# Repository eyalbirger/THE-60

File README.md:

The 60 is a split wireless/wired (pro micro and n!n) keyboard with mx switches, a screen option and harry potter art :)
its a lily58 like keyboard, but with an extra key and a stager that fits my hand better. maybe this will have a v3 with a knob (and more!), 
but i dont know if i want to spend money on that if this is a perfectly good keeb. anyway if there is a problem feel free to massege me.
i will not have a guide because realisticly im the only one thats ever gonna see this repo, so there is no point in having one. all the file
(and a complete bom) are also in here (https://www.nexprint.com/en/models/G7307162) so search it there. again im not gonna make a bom here cause 
no one is going to see this.

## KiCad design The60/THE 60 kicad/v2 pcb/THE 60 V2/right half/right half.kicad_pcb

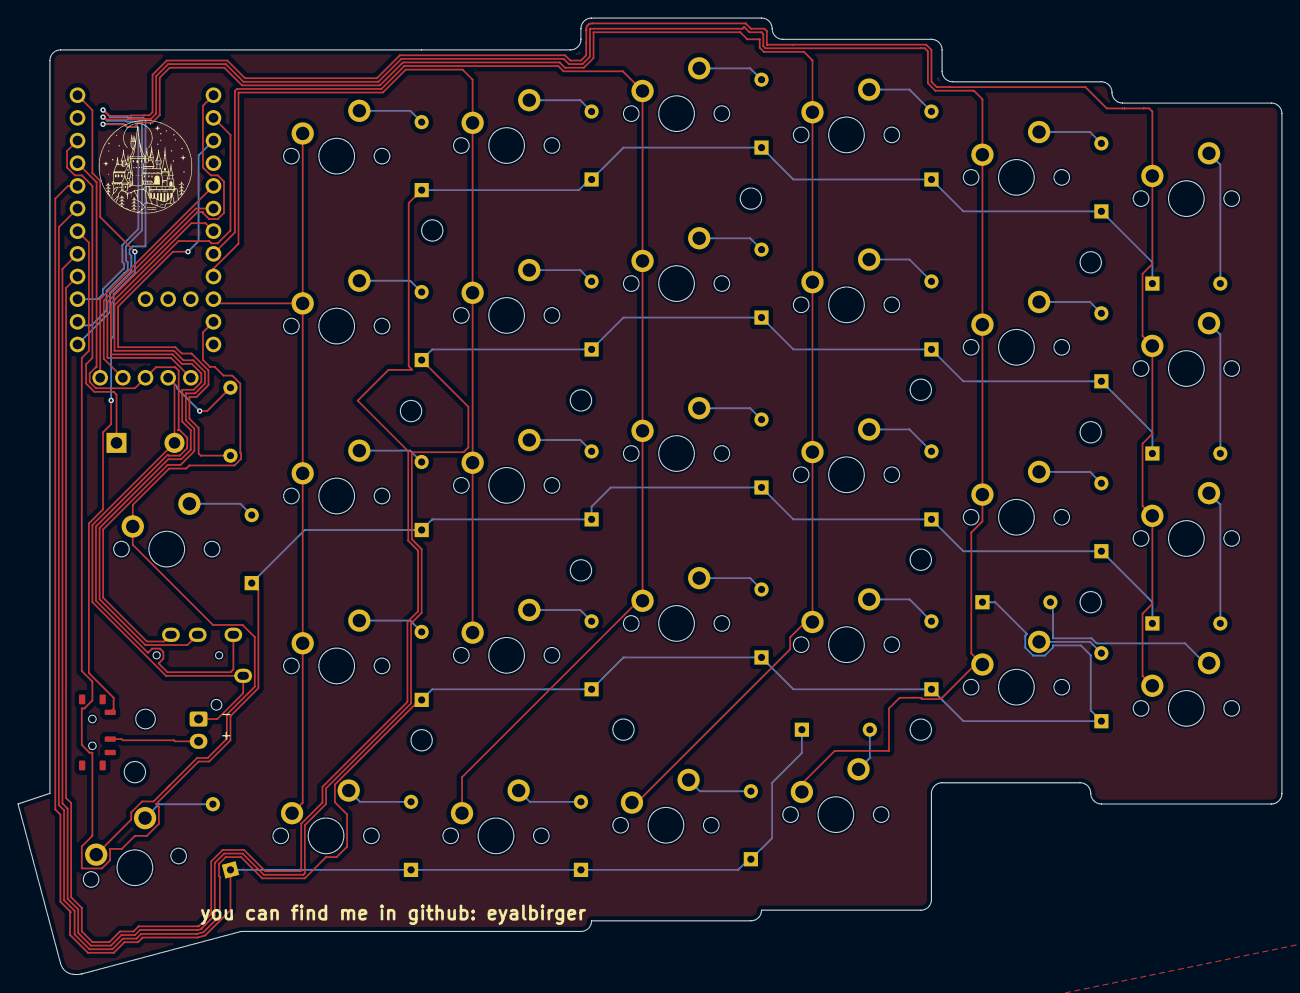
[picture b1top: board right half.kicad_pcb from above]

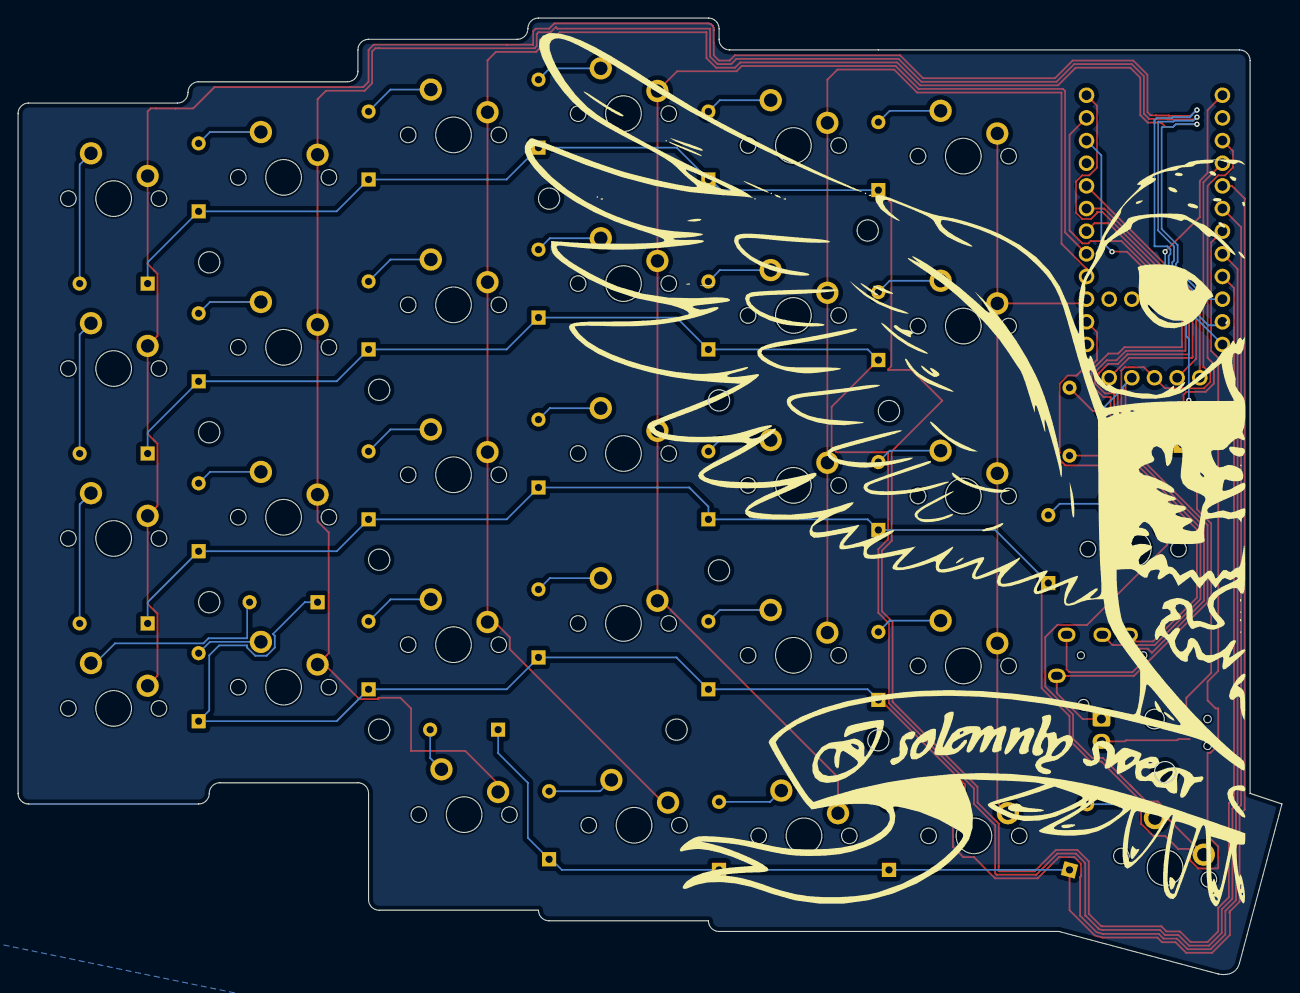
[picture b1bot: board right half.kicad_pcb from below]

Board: 2 copper layers, 141.7 x 107.2 mm, 68 parts (31 on the bottom side), 53 nets.

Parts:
D1, D2, D3, D4, D5, D6, D7, D8, D9, D10, D11, D12, D13, D14, D15, D16, D17, D18, D19, D20, D21, D22, D23, D24, D25, D26, D27, D28, D29, D59: Diode; Diode_DO-35
Display1: nice!view; nice_view
H6: MountingHole; MountingHole_2.2mm_M2
J1: Conn_01x02_Socket; JST_XH_B2B-XH-AM_1x02_P2.50mm_Vertical
R1: Resistor; R_Axial_DIN0207_L6.3mm_D2.5mm_P7.62mm_Horizontal
S1, S2, S3, S4, S5, S6, S7, S8, S9, S10, S11, S12, S13, S14, S15, S16, S17, S18, S19, S20, S21, S22, S23, S24, S25, S26, S27, S28, S29, S59: Keyswitch; MX_PCB_1.00u
SW1: Switch; Switch_MSK12C02
SW2: Switch; Button_MJTP1243
U2: Nice_Nano_V2; Nice_Nano_V2_Flipped
U3: TRRS; TRRS_PJ-320A

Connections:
19: U2.2 (0), U3.4 (RING2)
20: U2.7 (4), U3.3 (RING1)
+: J1.2, SW1.2
-: R1.1, U2.3 (GND)
unnamed: D1.2 (A), S1.2
unnamed: D2.2 (A), S2.2
unnamed: D3.2 (A), S3.2
unnamed: D4.2 (A), S4.2
unnamed: D5.2 (A), S5.2
unnamed: D6.2 (A), S6.2
unnamed: D7.2 (A), S7.2
unnamed: D8.2 (A), S8.2
unnamed: D9.2 (A), S9.2
unnamed: D10.2 (A), S10.2
unnamed: D11.2 (A), S11.2
unnamed: D12.2 (A), S12.2
unnamed: D13.2 (A), S13.2
unnamed: D14.2 (A), S14.2
unnamed: D15.2 (A), S15.2
unnamed: D16.2 (A), S16.2
unnamed: D17.2 (A), S17.2
unnamed: D18.2 (A), S18.2
unnamed: D19.2 (A), S19.2
unnamed: D20.2 (A), S20.2
unnamed: D21.2 (A), S21.2
unnamed: D22.2 (A), S22.2
unnamed: D23.2 (A), S23.2
unnamed: D24.2 (A), S24.2
unnamed: D25.2 (A), S25.2
unnamed: D26.2 (A), S26.2
unnamed: D27.2 (A), S27.2
unnamed: D28.2 (A), S28.2
unnamed: D29.2 (A), S29.2
unnamed: D59.2 (A), S59.2
b+: SW1.1, U2.24 (B+)
column 0: S1.1, S7.1, S13.1, S19.1, S59.1, U2.10 (7)
column 1: S2.1, S8.1, S14.1, S20.1, U2.9 (6)
column 2: S3.1, S9.1, S15.1, S21.1, S28.1, U2.8 (5)
column 3: S4.1, S10.1, S16.1, S22.1, S27.1, U2.15 (14)
column 4: S5.1, S11.1, S17.1, S23.1, S26.1, U2.14 (16)
column 5: S6.1, S12.1, S18.1, S24.1, U2.13 (10)
column -1: S25.1, S29.1, U2.11 (8)
cs: Display1.5 (CS), U2.1
gnd: Display1.4 (GND), J1.1, R1.2, SW2.2, U3.1 (SLEEVE)
mosi: Display1.1 (MOSI), U2.5 (2)
row 0: D1.1 (K), D2.1 (K), D3.1 (K), D4.1 (K), D5.1 (K), D6.1 (K), U2.16 (15)
row 1: D7.1 (K), D8.1 (K), D9.1 (K), D10.1 (K), D11.1 (K), D12.1 (K), U2.17 (18)
row 2: D13.1 (K), D14.1 (K), D15.1 (K), D16.1 (K), D17.1 (K), D18.1 (K), D25.1 (K), U2.18 (19)
row 3: D19.1 (K), D20.1 (K), D21.1 (K), D22.1 (K), D23.1 (K), D24.1 (K), U2.19 (20)
row 4: D26.1 (K), D27.1 (K), D28.1 (K), D29.1 (K), D59.1 (K), U2.20 (21)
rst: SW2.1, U2.22 (RST)
sck: Display1.2 (SCK), U2.6 (3)
vcc: Display1.3 (VCC), U2.21 (3.3v), U3.2 (TIP)

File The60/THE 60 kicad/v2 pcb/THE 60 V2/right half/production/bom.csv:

Designator,Footprint,Quantity,Value,LCSC Part #
"D1, D10, D11, D12, D13, D14, D15, D16, D17, D18, D19, D2, D20, D21, D22, D23, D24, D25, D26, D27, D28, D29, D3, D4, D5, D59, D6, D7, D8, D9",Diode_DO-35,30,Diode,
DISPLAY1,nice_view,1,nice!view,
J1,JST_XH_B2B-XH-AM_1x02_P2.50mm_Vertical,1,Conn_01x02_Socket,
R1,R_Axial_DIN0207_L6.3mm_D2.5mm_P7.62mm_Horizontal,1,Resistor,
"S1, S10, S11, S12, S13, S14, S15, S16, S17, S18, S19, S2, S20, S21, S22, S23, S24, S25, S26, S27, S28, S29, S3, S4, S5, S59, S6, S7, S8, S9",MX_PCB_1.00u,30,Keyswitch,
SW1,Switch_MSK12C02,1,Switch,
SW2,Button_MJTP1243,1,Switch,
U2,Nice_Nano_V2_Flipped,1,Nice_Nano_V2,
U3,TRRS_PJ-320A,1,TRRS,

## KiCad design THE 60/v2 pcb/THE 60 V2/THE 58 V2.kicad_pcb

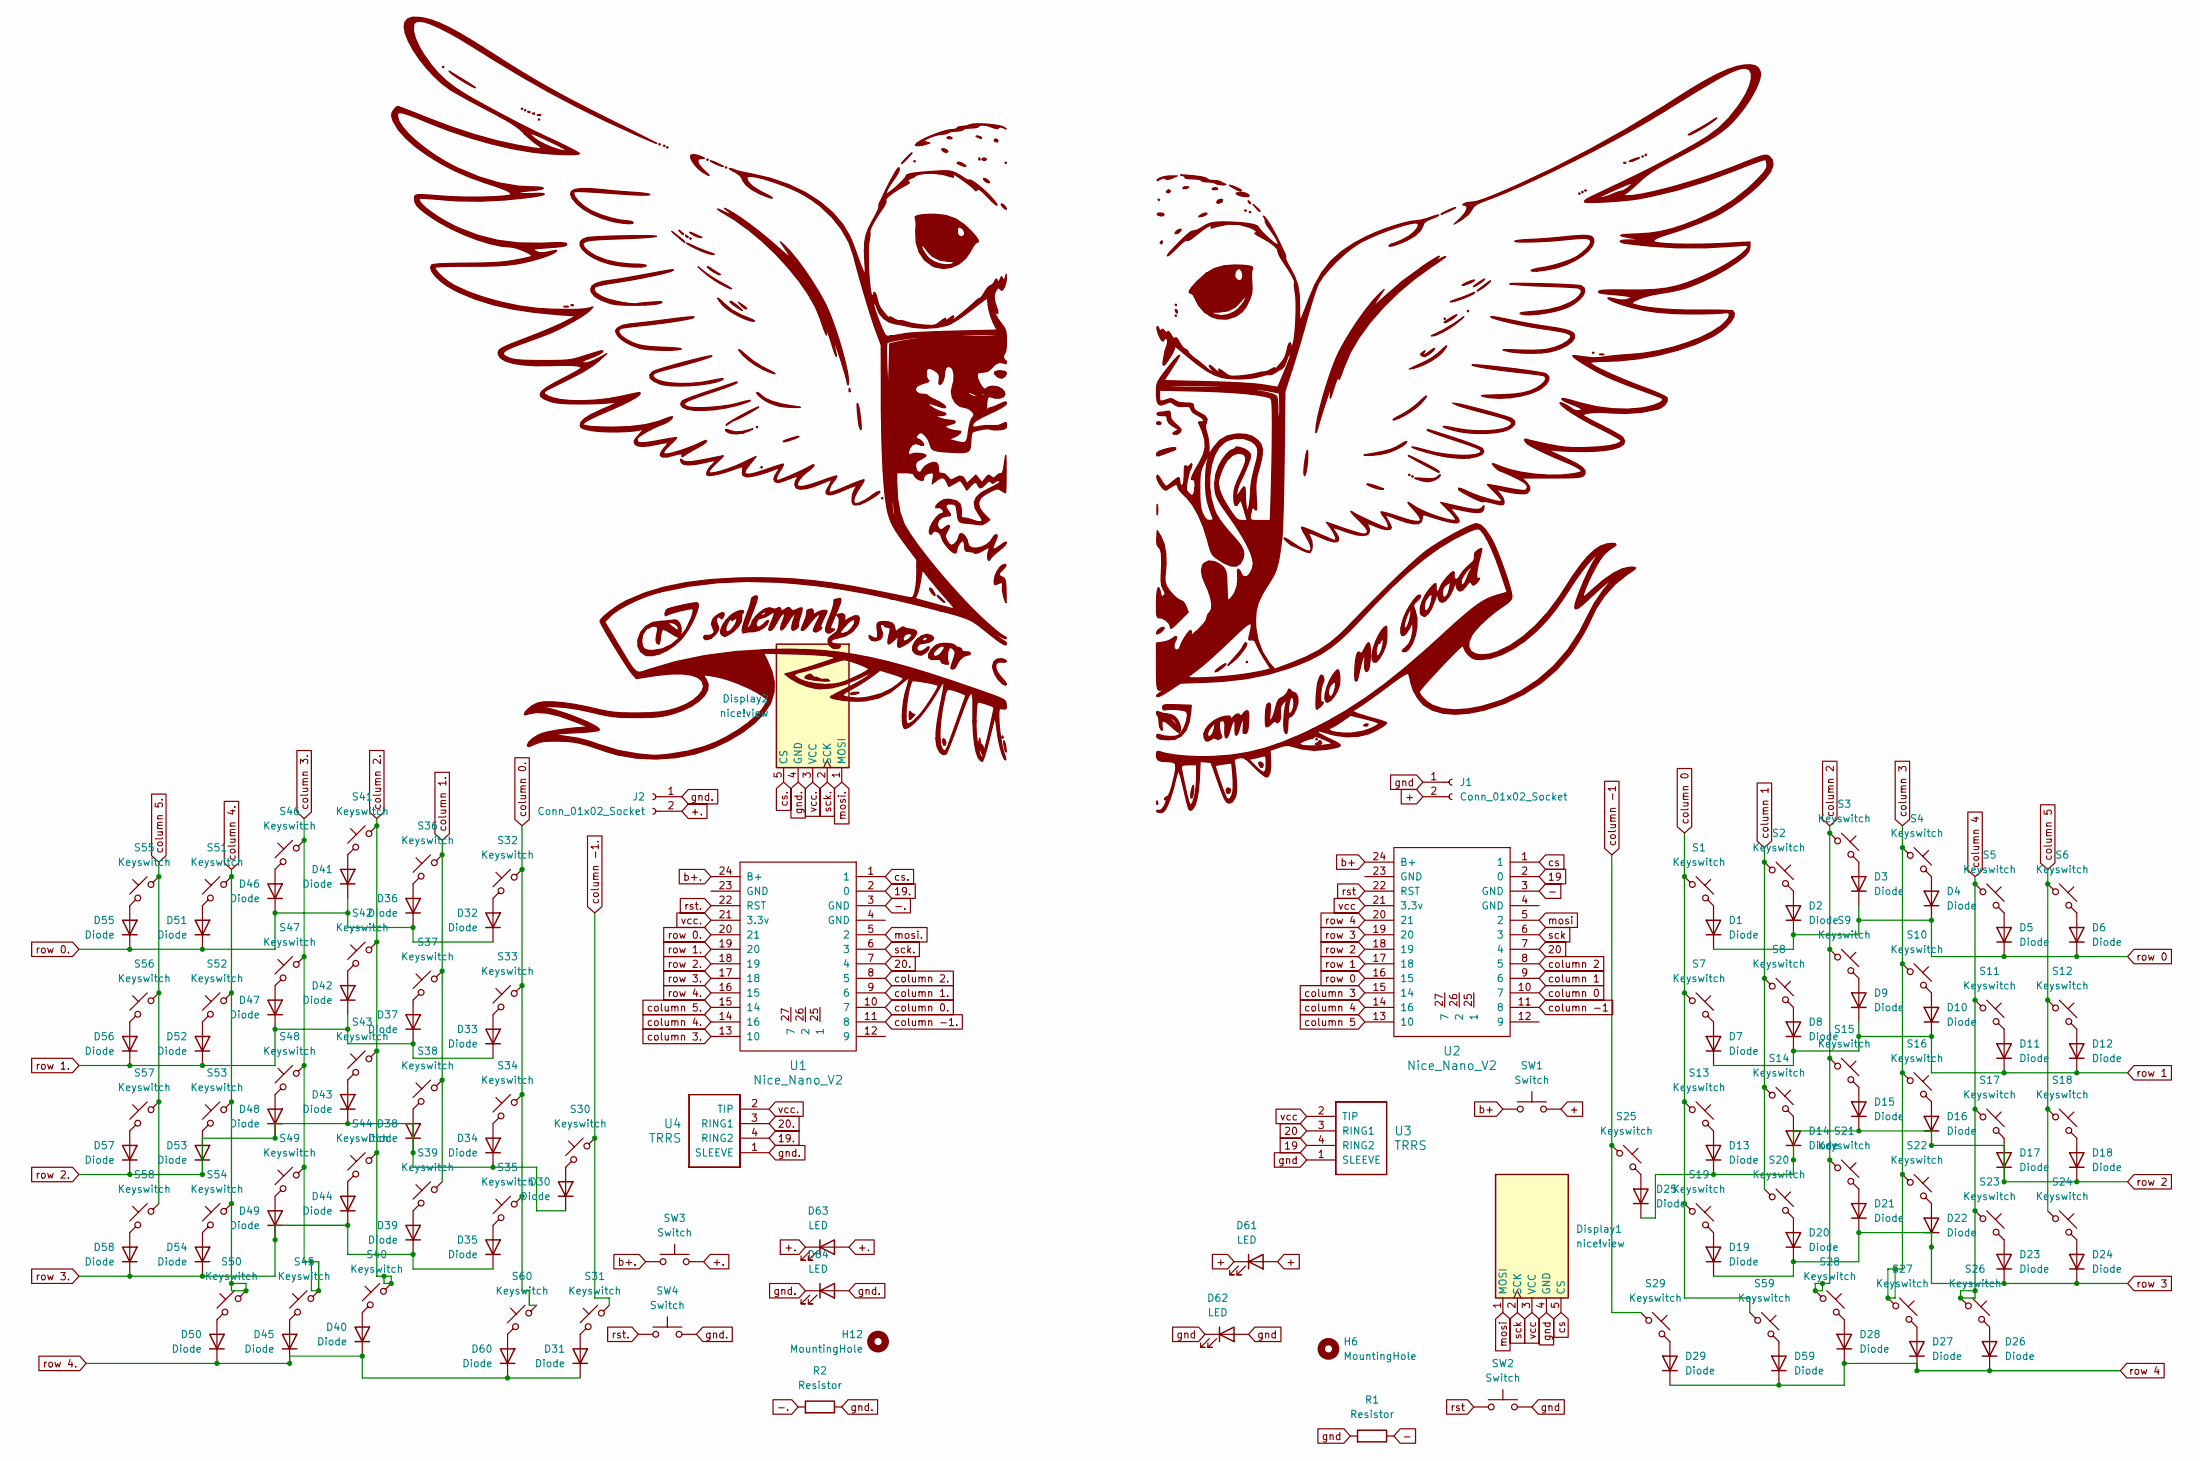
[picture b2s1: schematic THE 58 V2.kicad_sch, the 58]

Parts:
D1, D2, D3, D4, D5, D6, D7, D8, D9, D10, D11, D12, D13, D14, D15, D16, D17, D18, D19, D20, D21, D22, D23, D24, D25, D26, D27, D28, D29, D30, D31, D32, D33, D34, D35, D36, D37, D38, D39, D40, D41, D42, D43, D44, D45, D46, D47, D48, D49, D50, D51, D52, D53, D54, D55, D56, D57, D58, D59, D60: Diode; Diode_DO-35
D61, D62, D63, D64: LED; pad - oval2.5x1.5
Display1, Display2: nice!view; nice_view
H6, H12: MountingHole; MountingHole_2.2mm_M2
J1, J2: Conn_01x02_Socket; JST_XH_B2B-XH-AM_1x02_P2.50mm_Vertical
R1, R2: Resistor; R_Axial_DIN0207_L6.3mm_D2.5mm_P7.62mm_Horizontal
S1, S2, S3, S4, S5, S6, S7, S8, S9, S10, S11, S12, S13, S14, S15, S16, S17, S18, S19, S20, S21, S22, S23, S24, S25, S26, S27, S28, S29, S30, S31, S32, S33, S34, S35, S36, S37, S38, S39, S40, S41, S42, S43, S44, S45, S46, S47, S48, S49, S50, S51, S52, S53, S54, S55, S56, S57, S58, S59, S60: Keyswitch; MX_PCB_1.00u
SW1, SW3: Switch; Switch_MSK12C02
SW2, SW4: Switch; Button_MJTP1243
U1, U2: Nice_Nano_V2; Nice_Nano_V2_Flipped
U3, U4: TRRS; TRRS_PJ-320A

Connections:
19: U2.2 (0), U3.4 (RING2)
19.: U1.2 (0), U4.4 (RING2)
20: U2.7 (4), U3.3 (RING1)
20.: U1.7 (4), U4.3 (RING1)
+: D61.1 (K), D61.2 (A), J1.2, SW1.2
+.: D63.1 (K), D63.2 (A), J2.2, SW3.2
-: R1.1, U2.3 (GND)
-.: R2.2, U1.3 (GND)
unnamed: D1.2 (A), S1.2
unnamed: D2.2 (A), S2.2
unnamed: D3.2 (A), S3.2
unnamed: D4.2 (A), S4.2
unnamed: D5.2 (A), S5.2
unnamed: D6.2 (A), S6.2
unnamed: D7.2 (A), S7.2
unnamed: D8.2 (A), S8.2
unnamed: D9.2 (A), S9.2
unnamed: D10.2 (A), S10.2
unnamed: D11.2 (A), S11.2
unnamed: D12.2 (A), S12.2
unnamed: D13.2 (A), S13.2
unnamed: D14.2 (A), S14.2
unnamed: D15.2 (A), S15.2
unnamed: D16.2 (A), S16.2
unnamed: D17.2 (A), S17.2
unnamed: D18.2 (A), S18.2
unnamed: D19.2 (A), S19.2
unnamed: D20.2 (A), S20.2
unnamed: D21.2 (A), S21.2
unnamed: D22.2 (A), S22.2
unnamed: D23.2 (A), S23.2
unnamed: D24.2 (A), S24.2
unnamed: D25.2 (A), S25.2
unnamed: D26.2 (A), S26.2
unnamed: D27.2 (A), S27.2
unnamed: D28.2 (A), S28.2
unnamed: D29.2 (A), S29.2
unnamed: D30.2 (A), S30.2
unnamed: D31.2 (A), S31.2
unnamed: D32.2 (A), S32.2
unnamed: D33.2 (A), S33.2
unnamed: D34.2 (A), S34.2
unnamed: D35.2 (A), S35.2
unnamed: D36.2 (A), S36.2
unnamed: D37.2 (A), S37.2
unnamed: D38.2 (A), S38.2
unnamed: D39.2 (A), S39.2
unnamed: D40.2 (A), S40.2
unnamed: D41.2 (A), S41.2
unnamed: D42.2 (A), S42.2
unnamed: D43.2 (A), S43.2
unnamed: D44.2 (A), S44.2
unnamed: D45.2 (A), S45.2
unnamed: D46.2 (A), S46.2
unnamed: D47.2 (A), S47.2
unnamed: D48.2 (A), S48.2
unnamed: D49.2 (A), S49.2
unnamed: D50.2 (A), S50.2
unnamed: D51.2 (A), S51.2
unnamed: D52.2 (A), S52.2
unnamed: D53.2 (A), S53.2
unnamed: D54.2 (A), S54.2
unnamed: D55.2 (A), S55.2
unnamed: D56.2 (A), S56.2
unnamed: D57.2 (A), S57.2
unnamed: D58.2 (A), S58.2
unnamed: D59.2 (A), S59.2
unnamed: D60.2 (A), S60.2
b+: SW1.1, U2.24 (B+)
b+.: SW3.1, U1.24 (B+)
column 0: S1.1, S7.1, S13.1, S19.1, S59.1, U2.10 (7)
column 0.: S32.1, S33.1, S34.1, S35.1, S60.1, U1.10 (7)
column 1: S2.1, S8.1, S14.1, S20.1, U2.9 (6)
column 1.: S36.1, S37.1, S38.1, S39.1, U1.9 (6)
column 2: S3.1, S9.1, S15.1, S21.1, S28.1, U2.8 (5)
column 2.: S40.1, S41.1, S42.1, S43.1, S44.1, U1.8 (5)
column 3: S4.1, S10.1, S16.1, S22.1, S27.1, U2.15 (14)
column 3.: S45.1, S46.1, S47.1, S48.1, S49.1, U1.13 (10)
column 4: S5.1, S11.1, S17.1, S23.1, S26.1, U2.14 (16)
column 4.: S50.1, S51.1, S52.1, S53.1, S54.1, U1.14 (16)
column 5: S6.1, S12.1, S18.1, S24.1, U2.13 (10)
column 5.: S55.1, S56.1, S57.1, S58.1, U1.15 (14)
column -1: S25.1, S29.1, U2.11 (8)
column -1.: S30.1, S31.1, U1.11 (8)
cs: Display1.5 (CS), U2.1
cs.: Display2.5 (CS), U1.1
gnd: D62.1 (K), D62.2 (A), Display1.4 (GND), J1.1, R1.2, SW2.2, U3.1 (SLEEVE)
gnd.: D64.1 (K), D64.2 (A), Display2.4 (GND), J2.1, R2.1, SW4.2, U4.1 (SLEEVE)
mosi: Display1.1 (MOSI), U2.5 (2)
mosi.: Display2.1 (MOSI), U1.5 (2)
row 0: D1.1 (K), D2.1 (K), D3.1 (K), D4.1 (K), D5.1 (K), D6.1 (K), U2.16 (15)
row 0.: D32.1 (K), D36.1 (K), D41.1 (K), D46.1 (K), D51.1 (K), D55.1 (K), U1.20 (21)
row 1: D7.1 (K), D8.1 (K), D9.1 (K), D10.1 (K), D11.1 (K), D12.1 (K), U2.17 (18)
row 1.: D33.1 (K), D37.1 (K), D42.1 (K), D47.1 (K), D52.1 (K), D56.1 (K), U1.19 (20)
row 2: D13.1 (K), D14.1 (K), D15.1 (K), D16.1 (K), D17.1 (K), D18.1 (K), D25.1 (K), U2.18 (19)
row 2.: D30.1 (K), D34.1 (K), D38.1 (K), D43.1 (K), D48.1 (K), D53.1 (K), D57.1 (K), U1.18 (19)
row 3: D19.1 (K), D20.1 (K), D21.1 (K), D22.1 (K), D23.1 (K), D24.1 (K), U2.19 (20)
row 3.: D35.1 (K), D39.1 (K), D44.1 (K), D49.1 (K), D54.1 (K), D58.1 (K), U1.17 (18)
row 4: D26.1 (K), D27.1 (K), D28.1 (K), D29.1 (K), D59.1 (K), U2.20 (21)
row 4.: D31.1 (K), D40.1 (K), D45.1 (K), D50.1 (K), D60.1 (K), U1.16 (15)
rst: SW2.1, U2.22 (RST)
rst.: SW4.1, U1.22 (RST)
sck: Display1.2 (SCK), U2.6 (3)
sck.: Display2.2 (SCK), U1.6 (3)
vcc: Display1.3 (VCC), U2.21 (3.3v), U3.2 (TIP)
vcc.: Display2.3 (VCC), U1.21 (3.3v), U4.2 (TIP)

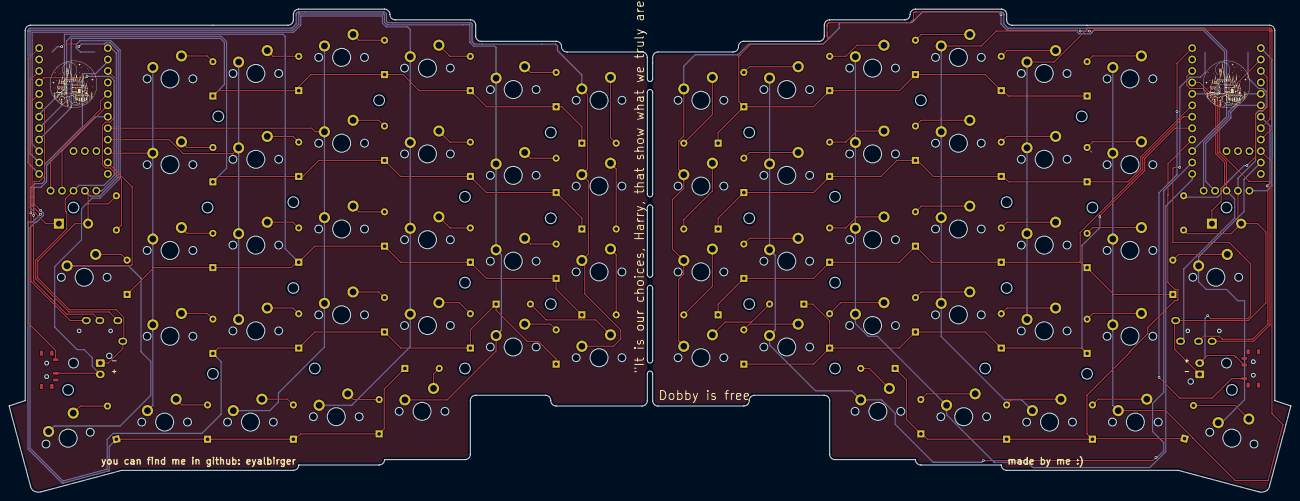
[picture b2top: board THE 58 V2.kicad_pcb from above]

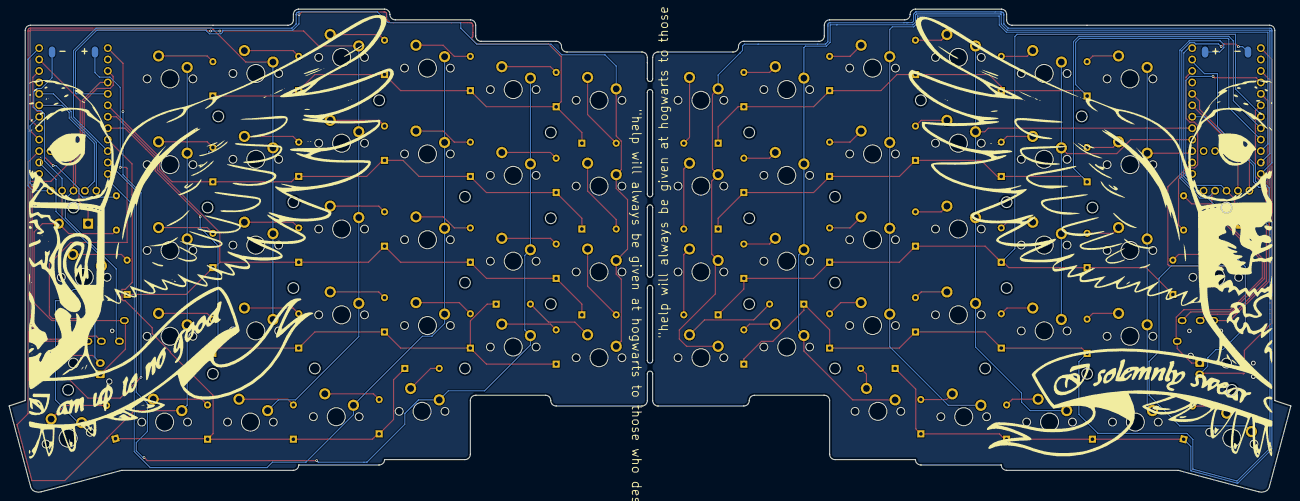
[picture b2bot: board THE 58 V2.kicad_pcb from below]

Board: 2 copper layers, 284.6 x 107.2 mm, 140 parts (66 on the bottom side), 106 nets.

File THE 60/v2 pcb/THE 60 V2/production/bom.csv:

Designator,Footprint,Quantity,Value,LCSC Part #
"D1, D10, D11, D12, D13, D14, D15, D16, D17, D18, D19, D2, D20, D21, D22, D23, D24, D25, D26, D27, D28, D29, D3, D30, D31, D32, D33, D34, D35, D36, D37, D38, D39, D4, D40, D41, D42, D43, D44, D45, D46, D47, D48, D49, D5, D50, D51, D52, D53, D54, D55, D56, D57, D58, D59, D6, D60, D7, D8, D9",Diode_DO-35,60,Diode,
"DISPLAY1, DISPLAY2",nice_view,2,nice!view,
"J1, J2",JST_XH_B2B-XH-AM_1x02_P2.50mm_Vertical,2,Conn_01x02_Socket,
"R1, R2",R_Axial_DIN0207_L6.3mm_D2.5mm_P7.62mm_Horizontal,2,Resistor,
"S1, S10, S11, S12, S13, S14, S15, S16, S17, S18, S19, S2, S20, S21, S22, S23, S24, S25, S26, S27, S28, S29, S3, S30, S31, S32, S33, S34, S35, S36, S37, S38, S39, S4, S40, S41, S42, S43, S44, S45, S46, S47, S48, S49, S5, S50, S51, S52, S53, S54, S55, S56, S57, S58, S59, S6, S60, S7, S8, S9",MX_PCB_1.00u,60,Keyswitch,
"SW1, SW3",Switch_MSK12C02,2,Switch,
"SW2, SW4",Button_MJTP1243,2,Switch,
"U1, U2",Nice_Nano_V2_Flipped,2,Nice_Nano_V2,
"U3, U4",TRRS_PJ-320A,2,TRRS,

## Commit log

2025-09-14 UPLOADED THE PCB AND THE SCHEM
2025-09-16 goo gaga
2025-09-17 updated the silk screen and stuff
2025-09-22 added a battery connector
    boo
2025-09-26 added 3d models
2025-09-26 mounting holes and outline change
2025-10-02 updated some stuff
2025-10-02 started the v2
2025-10-03 updated schem
2025-10-03 almost half way done pcb
2025-10-04 almost finished the pcb
2025-10-05 just finished every thingggggggg
2025-10-06 added silk screen
2025-10-07 another silk screen
2025-10-25 Panelized it
2025-11-02 /
    /
2025-11-07 finally finished this
2025-11-07 production file
2025-11-29 UPLOADED THE layout json
2025-11-29 added Hebrew and symbols
2025-11-30 made and uploaded the 3D files and made the layout in the keyboard layout editor site
2025-11-30 changed it from The60's build to M.Y.K.C
2025-12-06 bom, cad and multicolor
2025-12-07 updated cad
2026-01-09 uploaded the firmware
    Z
